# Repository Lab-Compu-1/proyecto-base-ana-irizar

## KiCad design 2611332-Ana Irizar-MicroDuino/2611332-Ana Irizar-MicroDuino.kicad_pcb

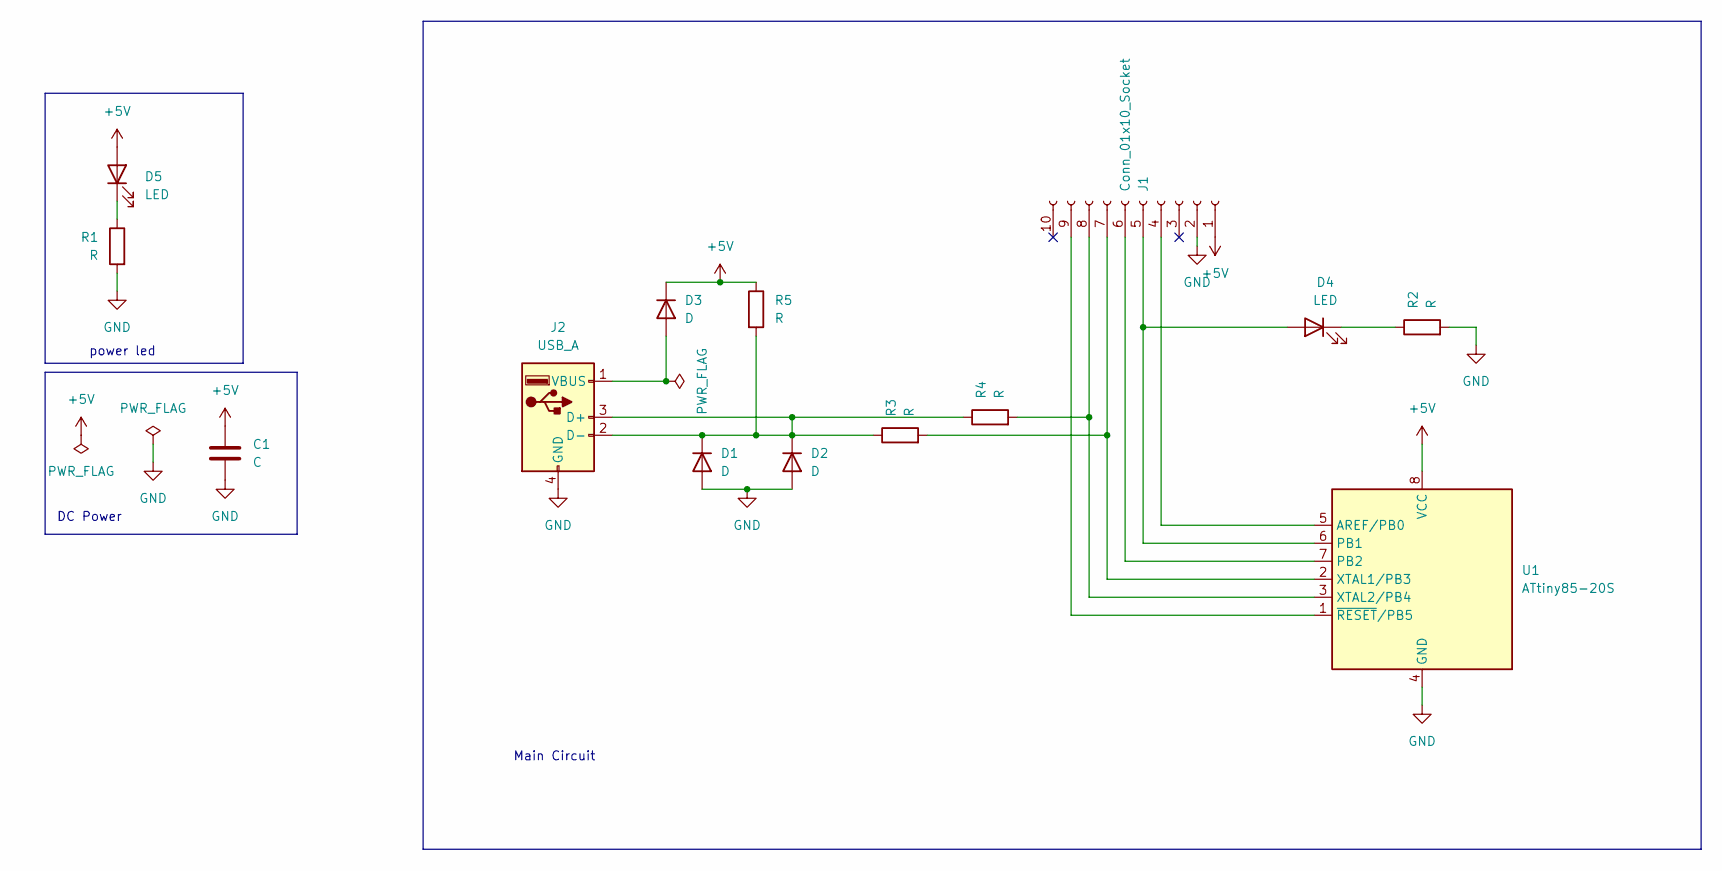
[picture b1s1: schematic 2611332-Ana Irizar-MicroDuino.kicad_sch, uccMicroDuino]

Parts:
C1: C; C_0805_2012Metric_Pad1.18x1.45mm_HandSolder
D1: D; D_MELF_Handsoldering
D2, D3: D; D_SOD-123
D4, D5: LED; ledSmd
J1: Conn_01x10_Socket; PinSocket_1x10_P2.54mm_Vertical
J2: USB_A; USB-A-PCB
R1, R2, R3, R4, R5: R; R_0805_2012Metric_Pad1.20x1.40mm_HandSolder
U1: ATtiny85-20S; SOIC-8_5.3x5.3mm_P1.27mm

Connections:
+5V: C1.1, D3.1 (K), D5.2 (A), J1.1, R5.1, U1.8 (VCC)
GND: C1.2, D1.2 (A), D2.2 (A), J1.2, J2.4 (GND), R1.2, R2.2, U1.4 (GND)
unnamed: D1.1 (K), D2.1 (K), J2.2 (D-), J2.3 (D+), R3.1, R4.1, R5.2
unnamed: D3.2 (A), J2.1 (VBUS)
unnamed: D4.2 (A), J1.5, U1.6 (PB1)
unnamed: D4.1 (K), R2.1
unnamed: D5.1 (K), R1.1
unnamed: J1.4, U1.5 (AREF/PB0)
unnamed: J1.6, U1.7 (PB2)
unnamed: J1.7, R3.2, U1.2 (XTAL1/PB3)
unnamed: J1.8, R4.2, U1.3 (XTAL2/PB4)
unnamed: J1.9, U1.1 (~RESET/PB5)

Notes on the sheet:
power led
DC Power
Main Circuit

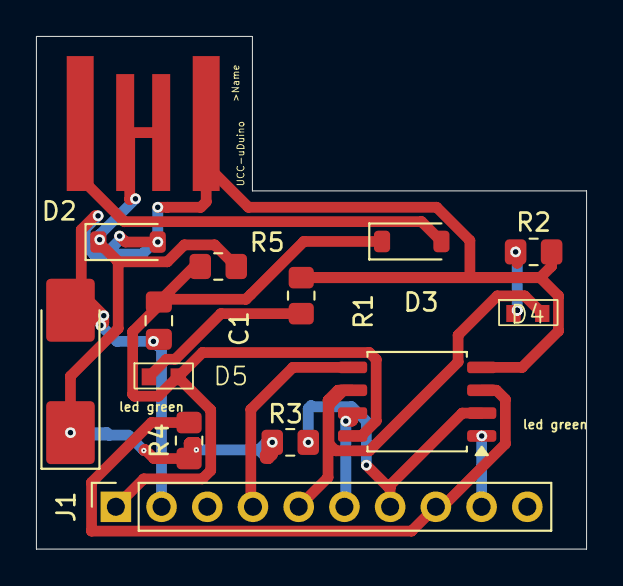
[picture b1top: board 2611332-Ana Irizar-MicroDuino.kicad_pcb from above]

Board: 2 copper layers, 30.6 x 28.5 mm, 14 parts (0 on the bottom side), 12 nets.

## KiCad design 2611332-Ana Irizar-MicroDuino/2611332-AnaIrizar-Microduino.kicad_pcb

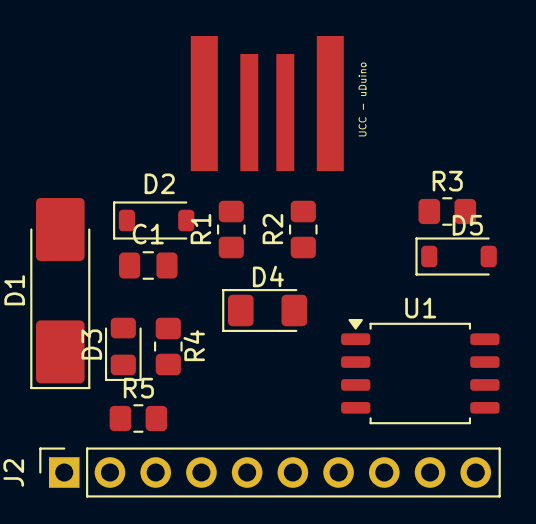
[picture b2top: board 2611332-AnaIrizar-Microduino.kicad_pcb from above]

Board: 2 copper layers, 14 parts (0 on the bottom side), 13 nets, no tracks yet.

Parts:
C1: C; C_0805_2012Metric_Pad1.18x1.45mm_HandSolder
D1: D; D_MELF_Handsoldering
D2, D5: D_Zener; D_SOD-123
D3: LED; LED_0805_2012Metric_Pad1.15x1.40mm_HandSolder
D4: LED; LED_1206_3216Metric_Pad1.42x1.75mm_HandSolder
J1: USB_A_UCC
J2: Conn_01x10_Socket; PinSocket_1x10_P2.54mm_Vertical
R1, R2, R3, R4, R5: R; R_0805_2012Metric_Pad1.20x1.40mm_HandSolder
U1: ATtiny85-20S; SOIC-8_5.3x5.3mm_P1.27mm

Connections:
+5V: C1.1, D1.1 (K), D4.2 (A), J2.1, R1.1, U1.8 (VCC)
GND: C1.2, D2.2 (A), D5.2 (A), J1.4 (GND), J2.2, R4.2, R5.2, U1.4 (GND)
unnamed: D1.2 (A), J1.1 (VBUS)
unnamed: D2.1 (K), J1.2 (D-), R1.2, R3.1
unnamed: D3.2 (A), J2.5, U1.6 (PB1)
unnamed: D3.1 (K), R4.1
unnamed: D4.1 (K), R5.1
unnamed: D5.1 (K), J1.3 (D+), R2.1
unnamed: J2.4, U1.5 (AREF/PB0)
unnamed: J2.6, U1.7 (PB2)
unnamed: J2.7, R3.2, U1.2 (XTAL1/PB3)
unnamed: J2.8, R2.2, U1.3 (XTAL2/PB4)
unnamed: J2.9, U1.1 (~RESET/PB5)

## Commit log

2026-05-29 GitHub Classroom Feedback
2026-05-29 Setting up GitHub Classroom Feedback
2026-05-29 mi primer commit y entrega de proyecto Kicad
2026-06-03 actualizo mi pcb
